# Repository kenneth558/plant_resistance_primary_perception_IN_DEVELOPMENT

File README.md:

[Project now moved to wiki.  Simply click here](https://github.com/kenneth558/plant_resistance_primary_perception/wiki/Entanglement-GWAAMC), and thank you for correcting your link records!

[Project purchase and building instructions here](https://github.com/kenneth558/plant_resistance_primary_perception/tree/Free/Where%20to%20find%20everything%20for%20making%20your%20own%20GWAAMC%20device)

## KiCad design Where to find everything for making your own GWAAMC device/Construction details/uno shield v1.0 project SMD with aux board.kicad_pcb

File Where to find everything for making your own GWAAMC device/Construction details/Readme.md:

The U numbers in these depictions are off by one since the U numbering scheme changed 06 Sep 2019

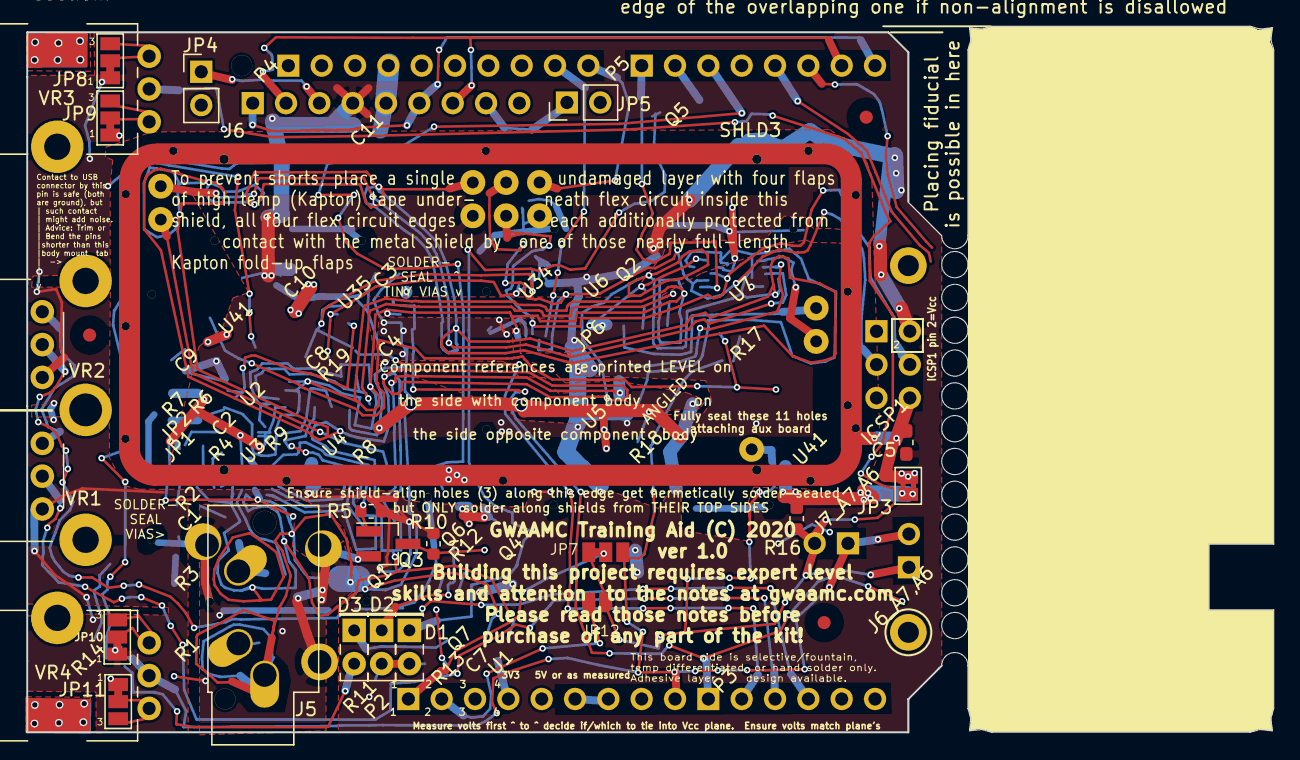
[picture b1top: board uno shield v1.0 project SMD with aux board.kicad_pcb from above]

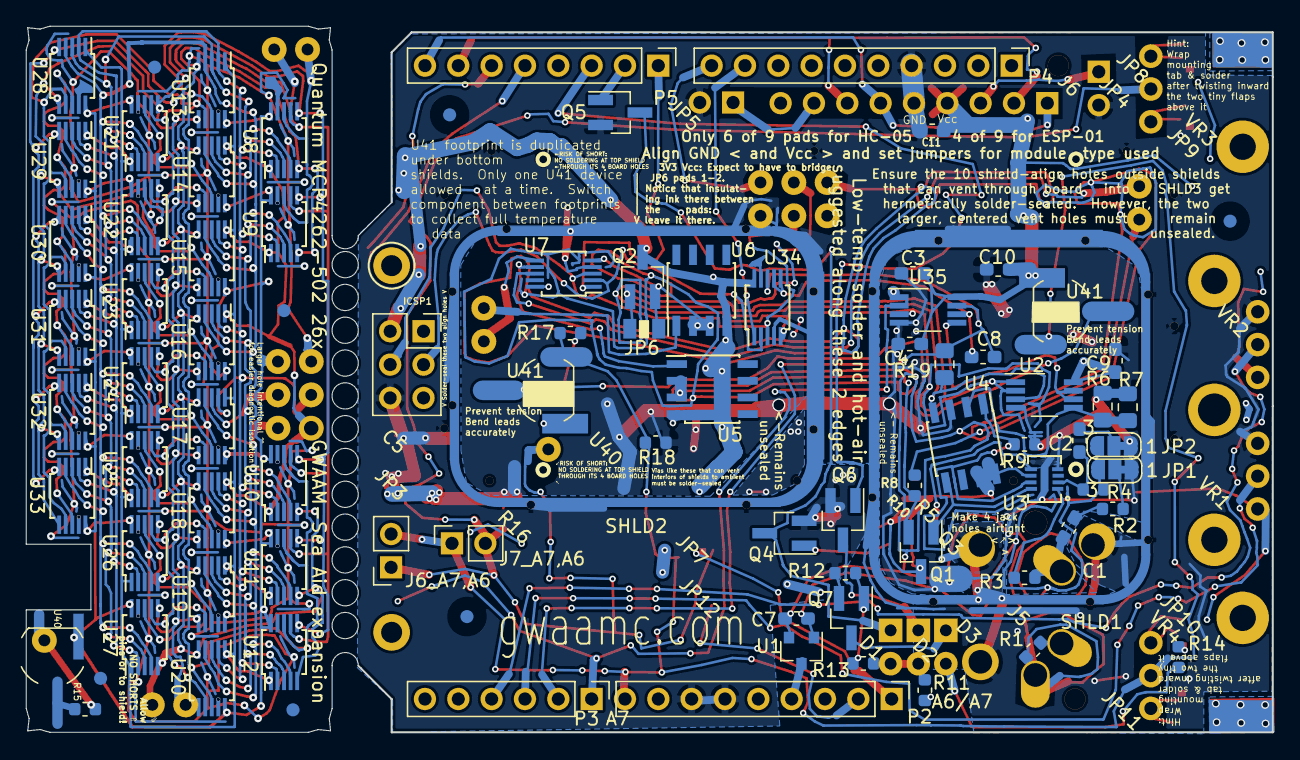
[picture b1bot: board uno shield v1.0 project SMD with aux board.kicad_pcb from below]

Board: 2 copper layers, 95.0 x 53.8 mm, 169 parts (100 on the bottom side), 59 nets.

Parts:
BreakGuide: MountingHole_2.1mm; BreakguideHole
BreakGuide#2, BreakGuide#3, BreakGuide#4, BreakGuide#5, BreakGuide#6, BreakGuide#7, BreakGuide#8, BreakGuide#9, BreakGuide#10, BreakGuide#11, BreakGuide#12, BreakGuide#13, BreakGuide#14, BreakGuide#15, BreakGuide#16, BreakGuide#17, BreakGuide#18, BreakGuide#19, BreakGuide#20, BreakGuide#21, BreakGuide#22, BreakGuide#23, BreakGuide#24, BreakGuide#25, BreakGuide#26, BreakGuide#27, BreakGuide#28: MountingHole_2.1mm; BreakguideHole
C1: 390 pF; C_0603_1608Metric_Pad1.05x0.95mm_HandSolder
C2: .22 µF; C_0603_1608Metric_Pad1.05x0.95mm_HandSolder
C3, C5: 10 µF; C_0603_1608Metric_Pad1.05x0.95mm_HandSolder
C4, C11: 0.1 µF; C_0603_1608Metric_Pad1.05x0.95mm_HandSolder
C7: 1uF; C_0603_1608Metric_Pad1.05x0.95mm_HandSolder
C8: 10-51 pF; C_0603_1608Metric_Pad1.05x0.95mm_HandSolder
C9, C10: .022 µF; C_0603_1608Metric_Pad1.05x0.95mm_HandSolder
D1: Red: Electrodes shorted; LED_Rectangular_W5.0mm_H2.0mm
D2: Yellow: Inadequate electrode conductance; LED_Rectangular_W5.0mm_H2.0mm_yellow
D3: Green: Proper electrode conductance; LED_Rectangular_W5.0mm_H2.0mm_green
FID1, FID2, FID3, FID4, FID5, FID6: Fiducial_1mm_Mask3mm
FID 7, FID 7#2, FID 7#3, FID 88: Fiducial_1mm_Mask3mm
ICSP1: ICSP Socket; PinSocket_2x03_P2.54mm_Vertical
J1, J2, J3, J4: CONN_01X01; TestPoint_Keystone_5010-5014_Multipurpose
J5: Conn_3.5mm; Jack_3.5mm_CUI_SJ1-3534NS_Horizontal_CircularHoles
J6: Conn_01x09_Female; PinSocket_1x09_P2.54mm_Vertical
J6_A7,A6: Conn_01x02_Male; PinSocket_1x02_P2.54mm_Vertical
J7, J8, J9, J10, J11, J12, J13, J14, J15, J16, J17: Conn_01x01_Male; Hole_0.5mm
J7_A7,A6: Conn_01x02_Female; PinSocket_1x02_P2.54mm_Vertical
J17#2, J18, J19, J20, J23, J24, J24#2, J24#3, J24#4, J25, J32: Conn_01x01_Male; Banana_Jack_2mm_1Pin
JP1: C1_leak_mitigator; SolderJumper-3_P1.3mm_Bridged12_RoundedPad1.0x1.5mm_NumberL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
JP2: C2_bias_reducer; SolderJumper-3_P1.3mm_Bridged12_RoundedPad1.0x1.5mm_NumberL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
JP3: Cut_JP3_if_installing_HX711_option; SolderJumper-2_P1.3mm_Bridged2Bar_Pad1.0x1.5mm
JP4: HC-05_EN/KEY; PinHeader_1x02_P2.54mm_Vertical
JP5: HC-05_KEY/STATE_LED; PinHeader_1x02_P2.54mm_Vertical
JP6: Bridge in 3Vdc; SolderJumper-2_P1.3mm_Open_Pad1.0x1.5mm
JP7: SolderJumper_3_Bridged12; SolderJumper-3_P1.3mm_Bridged12_Pad1.0x1.5mm
JP8, JP9, JP10, JP11: SolderJumper_3_Bridged12; SolderJumper-3_P1.3mm_Bridged12_Pad1.0x1.5mm_NumberLabels
JP12: SolderJumper_2_Open; SolderJumper-2_P1.3mm_Open_RoundedPad1.0x1.5mm
P2: Power; PinHeader_1x09_P2.54mm_Vertical
P3: Analog; PinHeader_1x06_P2.54mm_Vertical
P4: Digital; PinHeader_1x10_P2.54mm_Vertical
P5: Digital; PinHeader_1x08_P2.54mm_Vertical
Q1, Q2: MMBF5460 (2N5460); SOT-23_Handsoldering
Q3, Q4, Q5, Q6, Q7: DMN601K-7; SOT-23_Handsoldering
R1, R2: 100 Ω; R_0603_1608Metric
R3: 3.9 KΩ; R_0603_1608Metric
R4: 21 KΩ; R_0603_1608Metric
R5, R9: 10 KΩ; R_0603_1608Metric
R6: 44.2 KΩ 0.1% 0.1W(1/10W) ±10ppm/°C (1676343-2); R_0805_2012Metric_Pad1.15x1.40mm_HandSolder
R7: 22.6 KΩ 0.1% 0.125W(1/8W) ±10ppm/°C (ERA6ARB2262V); R_0805_2012Metric_Pad1.15x1.40mm_HandSolder
R8: 15 KΩ; R_0603_1608Metric
R10, R12, R13: 1 MΩ; R_0603_1608Metric
R11, R14: 470 Ω; R_0603_1608Metric
R15, R17: 14.7 KΩ 0.1% 0.063W ±25ppm/°C (NTR06B1472CTRF); R_0603_1608Metric
R16, R18: 390 KΩ 0.1% 0.063W ±25ppm/°C (CPF0603B390KE1); R_0603_1608Metric
R19: Optional_Rf; R_0805_2012Metric_Pad1.15x1.40mm_HandSolder
SHLD1, SHLD2: MS263-20C (cover only of MS263-20); Masach_Tech_MS26320_26x19.50mm
SHLD3: MS544-10C (cover only of MS544-10); Masach_Tech_MS54410_54x23.90mm
U1: 3V LDO; SOT-23
U2, U35: OPA2388IDGKR; VSSOP-8_3.0x3.0mm_P0.65mm
U3: ADL5315; ADL5315ACPZ-R7
U4: REF200AU; SOIC-8_3.9x4.9mm_P1.27mm
U5, U6: LM334M; SOIC-8_3.9x4.9mm_P1.27mm
U7: MCP4262-503E/UN; MSOP-10_3x3mm_P0.5mm
U8, U9, U10, U11, U12, U13, U14, U15, U16, U17, U18, U19, U20, U21, U22, U23, U24, U25, U26, U27, U28, U29, U30, U31, U32, U33, U34: MCP4262-502E/UN; MSOP-10_3x3mm_P0.5mm
U40: LM334Z; TO-92_Spread_for_LM334Z
U41, U41#2: LM334Z; TO-92_full pads_for_LM334Z
VR1, VR2: 50 KΩ; Potentiometer_Bourns_PTV09A-2_Single_Horizontal
VR3, VR4: 20 KΩ; Potentiometer_Bourns_PTV09A-1_Single_Vertical

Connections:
+3V3: P2.4, U1.3
/1st_stage_guard_ring: C7.1, J12.1, J24#3.1, JP1.3, JP2.3, R4.2, U1.2
/2nd_stage_ring: R9.1, U3.7, U4.1
/3rd_stage_guard_ring: U2.1, U2.2, U34.5, U35.3
/5(**): P5.3, Q6.1
/6(**): P5.2, Q5.1
/7: P5.1, U7.1
/8: J14.1, J23.1, P4.10, U8.1, U9.1, U10.1, U11.1, U12.1, U13.1, U14.1, U15.1, U16.1, U17.1, U18.1, U19.1, U20.1, U21.1, U22.1, U23.1, U24.1, U25.1, U26.1, U27.1, U28.1, U29.1, U30.1, U31.1, U32.1, U33.1
/9(**): P4.9, U34.1
/A0: P3.1, U35.1, U35.2
/A1: C8.1, P3.2, R19.1, U34.8, U35.7
/A2: P3.3, VR1.2
/A3: P3.4, VR2.2
/A6: J6_A7,A6.1, J7_A7,A6.2, J17.1, J17#2.1, JP7.1, JP12.2, R15.2, R16.1, U40.3, VR3.2
/A6-A7: JP7.2, P2.1
/A7: J6_A7,A6.2, J7_A7,A6.1, JP7.3, P2.9, R17.2, R18.1, U41.3, U41#2.3, VR4.2
/CFG-IOREF-A6: JP12.1, P2.2
/J5-PadR: C1.1, J5.R, R3.1
/J5-PadT: J5.T, R1.2
/MOSI(1): ICSP1.4, J16.1, J24#2.1, U7.3, U8.3, U9.3, U10.3, U11.3, U12.3, U13.3, U14.3, U15.3, U16.3, U17.3, U18.3, U19.3, U20.3, U21.3, U22.3, U23.3, U24.3, U25.3, U26.3, U27.3, U28.3, U29.3, U30.3, U31.3, U32.3, U33.3, U34.3
/Rx: J6.1, J6.6, P5.8
/SCK(1): ICSP1.3, J15.1, J25.1, U7.2, U8.2, U9.2, U10.2, U11.2, U12.2, U13.2, U14.2, U15.2, U16.2, U17.2, U18.2, U19.2, U20.2, U21.2, U22.2, U23.2, U24.2, U25.2, U26.2, U27.2, U28.2, U29.2, U30.2, U31.2, U32.2, U33.2, U34.2
/Tx: J6.2, J6.7, P5.7
/U8-Pad5: J8.1, J19.1, U7.6, U8.5, U9.5, U10.5, U11.5, U12.5, U13.5, U14.5, U15.5, U16.5, U17.5, U18.5, U19.5, U20.5, U21.5, U22.5, U23.5, U24.5, U25.5, U26.5, U27.5, U28.5, U29.5, U30.5, U31.5, U32.5, U33.5
/U8-Pad6: J7.1, J20.1, U6.1, U8.6, U9.6, U10.6, U11.6, U12.6, U13.6, U14.6, U15.6, U16.6, U17.6, U18.6, U19.6, U20.6, U21.6, U22.6, U23.6, U24.6, U25.6, U26.6, U27.6, U28.6, U29.6, U30.6, U31.6, U32.6, U33.6
/U8-Pad7: J10.1, J32.1, R8.1, U8.7, U9.7, U10.7, U11.7, U12.7, U13.7, U14.7, U15.7, U16.7, U17.7, U18.7, U19.7, U20.7, U21.7, U22.7, U23.7, U24.7, U25.7, U26.7, U27.7, U28.7, U29.7, U30.7, U31.7, U32.7, U33.7
/U8-Pad8: J11.1, J18.1, U7.8, U8.8, U9.8, U10.8, U11.8, U12.8, U13.8, U14.8, U15.8, U16.8, U17.8, U18.8, U19.8, U20.8, U21.8, U22.8, U23.8, U24.8, U25.8, U26.8, U27.8, U28.8, U29.8, U30.8, U31.8, U32.8, U33.8
GNDA: C3.2, C4.2, C7.2, C9.1, C10.1, J5.S, JP1.1, JP2.1, JP3.1, R1.1, R6.2, R7.2, R9.2, R16.2, R18.2, U1.1, U2.4, U3.4, U3.9, U4.3, U35.4
GNDD: C5.2, C11.1, ICSP1.6, J5.G, J6.5, J13.1, J24.1, JP3.2, JP4.2, JP5.2, JP9.1, JP11.1, P2.6, P2.7, P4.4, Q3.2, Q4.2, Q5.2, Q6.2, Q7.2, R12.1, SHLD1.1, SHLD2.1, SHLD3.1, U7.4, U8.4, U9.4, U10.4, U11.4, U12.4, U13.4, U14.4, U15.4, U16.4, U17.4, U18.4, U19.4, U20.4, U21.4, U22.4, U23.4, U24.4, U25.4, U26.4, U27.4, U28.4, U29.4, U30.4, U31.4, U32.4, U33.4, U34.4, VR1.1, VR2.1
unnamed: C1.2, R2.1
unnamed: C2.1, R4.1, U3.2
unnamed: C2.2, JP2.2
unnamed: C8.2, U34.6, U34.7, U35.6
unnamed: D1.1, Q4.3, Q5.3
unnamed: D1.2, D2.2, R11.2, R13.2
unnamed: D2.1, Q6.3
unnamed: D3.1, Q7.3
unnamed: D3.2, R14.2
unnamed: J6.3, JP4.1
unnamed: J6.8, JP5.1
unnamed: JP1.2, R2.2
unnamed: JP6.1, Q2.2, U6.2, U6.3, U7.5
unnamed: JP6.2, Q2.1, R19.2, U2.3, U4.4
unnamed: JP8.2, JP8.3, VR3.3
unnamed: JP9.2, JP9.3, VR3.1
unnamed: JP10.2, JP10.3, VR4.3
unnamed: JP11.2, JP11.3, VR4.1
unnamed: Q1.1, U3.8, U4.5
unnamed: Q1.2, R8.2, U5.2, U5.3
unnamed: Q3.1, R5.1, U3.5
unnamed: Q3.3, Q4.1, R10.2
unnamed: Q7.1, R12.2, R13.1
unnamed: R3.2, U3.1
unnamed: R6.1, R7.1, U2.5, U4.2
unnamed: R15.1, U40.2
unnamed: R17.1, U41.2, U41#2.2
unnamed: U2.6, U2.7, U35.5
unnamed: U5.1, U7.7
VCC: C3.1, C4.1, C5.1, C9.2, C10.2, C11.2, ICSP1.2, J6.4, J9.1, J24#4.1, JP8.1, JP10.1, Q1.3, Q2.3, R5.2, R10.1, R11.1, R14.1, U2.8, U3.6, U4.7, U4.8, U5.4, U6.4, U7.10, U8.10, U9.10, U10.10, U11.10, U12.10, U13.10, U14.10, U15.10, U16.10, U17.10, U18.10, U19.10, U20.10, U21.10, U22.10, U23.10, U24.10, U25.10, U26.10, U27.10, U28.10, U29.10, U30.10, U31.10, U32.10, U33.10, U34.10, U35.8, U40.1, U41.1, U41#2.1, VR1.3, VR2.3

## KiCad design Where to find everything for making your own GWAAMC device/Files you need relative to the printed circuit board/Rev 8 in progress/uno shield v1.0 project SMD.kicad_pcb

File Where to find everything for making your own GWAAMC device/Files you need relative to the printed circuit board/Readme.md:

To buy your own PCB you'll send [this file](https://github.com/kenneth558/plant_resistance_primary_perception/blob/Free/Where%20to%20find%20everything%20for%20making%20your%20own%20GWAAMC%20device/Files%20you%20need%20relative%20to%20the%20printed%20circuit%20board/v1.0/gerbers%20uno%20shield%20v1.0%20main%20board%20only.zip) and [this file](https://github.com/kenneth558/plant_resistance_primary_perception/blob/Free/Where%20to%20find%20everything%20for%20making%20your%20own%20GWAAMC%20device/Files%20you%20need%20relative%20to%20the%20printed%20circuit%20board/v1.0/Quantum%20MCP4262-502%2026x%20expansion%20for%20GWAAM-Sea%20Aid%20gerbers.zip) to OSH Park, BasicPCB, PCBWay, or to wherever you choose, then pay and wait.  [This](https://oshpark.com/shared_projects/fb4IIqwY) is the OSH Park project link for even easier ordering of the main board...and [aux board](https://oshpark.com/shared_projects/tLj5WHoL) at OSH Park. A minimum quantity purchase of 3-5 boards is normal.  

*NEW!* [Boards combined](https://github.com/kenneth558/plant_resistance_primary_perception/blob/Free/Where%20to%20find%20everything%20for%20making%20your%20own%20GWAAMC%20device/Files%20you%20need%20relative%20to%20the%20printed%20circuit%20board/v1.0/combined%20main%20plus%20aux%20on%20single%20board/gerbers%20uno%20shield%20v1.0%20PCB%20sections%20combined.zip) but able to be carefully separated before or after after components get soldered down.  May be temporarily air-wired into operation while still in one piece.  This style may help you in PCB soliciting quotes and ordering, but it will be risky separating them due to proximity to board edges of conducting traces.  [Boards combined OSH Park project](https://oshpark.com/shared_projects/ZdywHSTk).

I actually can't recommend the ENIG boards because industry wisdom is now that the gold on ENIG boards is better washed off ("cleansed") by double tinning - I've found that I have to wash it off, anyway, to get acceptable results.  That negates the entire advantage of ENIG's flat pads for fine pitch components because it takes several hours to double tin and flatten out the pads.  Then on top of that, the last HASL boards I ordered had taken sufficient precautions to give me flat pads on the side of the board it mattered most for me...without me even suggesting it!  That left only one single fine-pich component for me to worry about, and I took care of that easily with Kapton tape/hot air/hot iron pad flattening.  Besides, ENIG boards are limited to a six month shelf life.  So I'm going to recommend just getting 2oz,TG170+, lead-free HASL boards, requesting the fab house try to put flattest pads on the surface with the most fine-pitch packages, and flatten any other fine pitch pads yourself.  On the ENIG boards, a little solder flux helps conduct the heat and makes things less frustrating.  If there is any chance you'll use bismuth solder and you're going the HASL route, specify "lead-free" HASL or the solder won't stick to the pads.

If you are determined to purchase ENIG boards, you can't go wrong with OSH Park because their [rigid] boards handle the heat so well without the copper delaminating nor heat damage occuring otherwise.  I've read they use TG170.  Chinese boards default to TG140 and will darken and char at much lower heat levels than OSH Park boards, and their copper delaminates from the board at lower heat levels than OSH Park's 2 oz. boards.  OSH Park's flex boards, however, won't handle full-scale air heating without risking bubbles, but if you're careful to pop those bubbles while they're small, you should be fine.

When I got sloppy with the ENIG boards by putting on way more solder than I needed to, I did pull pads up, so you might as well be neat and frugal while tinning, including only tinning one side - the side you need to tin - on the plated through holes.  Here's how I convert ENIG to lead-free HASL:  
- I use hot air, 
- press lead-free solid wire solder against all gold that needs to be soldered to until the gold is absorbed into molten solder
- I do this twice
- I scoop the surface flat with hot air, then convert to bismuth (low temperature) solder with one more pass and scoop flat again.  If you've been thorough on every step, your board is ready to accept bismuth cream and placed components and heat to melt the low-temperature solder.

Stencil stock thickness should be no more than 4 mil (0.1mm).  Don't trust stacking stencils to obtain that thickness because the stencil apertures must have smooth enough walls not to pull the paste solder off the board when removed.  Remove the stencil quick enough after applying the paste that the paste doesn't dry enough to adhere to the stencil apertures walls.

Stencils are [here](https://github.com/kenneth558/plant_resistance_primary_perception/blob/Free/Where%20to%20find%20everything%20for%20making%20your%20own%20GWAAMC%20device/Files%20you%20need%20relative%20to%20the%20printed%20circuit%20board/v1.0/F%26B%20Paste%20stencils%20uno%20shield%20v1.0%20main%20board%20only.zip).

*NEW!* Combined board stencils [here](https://github.com/kenneth558/plant_resistance_primary_perception/blob/Free/Where%20to%20find%20everything%20for%20making%20your%20own%20GWAAMC%20device/Files%20you%20need%20relative%20to%20the%20printed%20circuit%20board/v1.0/combined%20main%20plus%20aux%20on%20single%20board/F%26B%20Paste%20stencils%20uno%20shield%20v1.0%20PCB%20sections%20combined.zip).

Bare board renderings courtesy of OSH Park

[Go to populating the board or the populated board instead](https://github.com/kenneth558/plant_resistance_primary_perception/tree/Free/Where%20to%20find%20everything%20for%20making%20your%20own%20GWAAMC%20device)

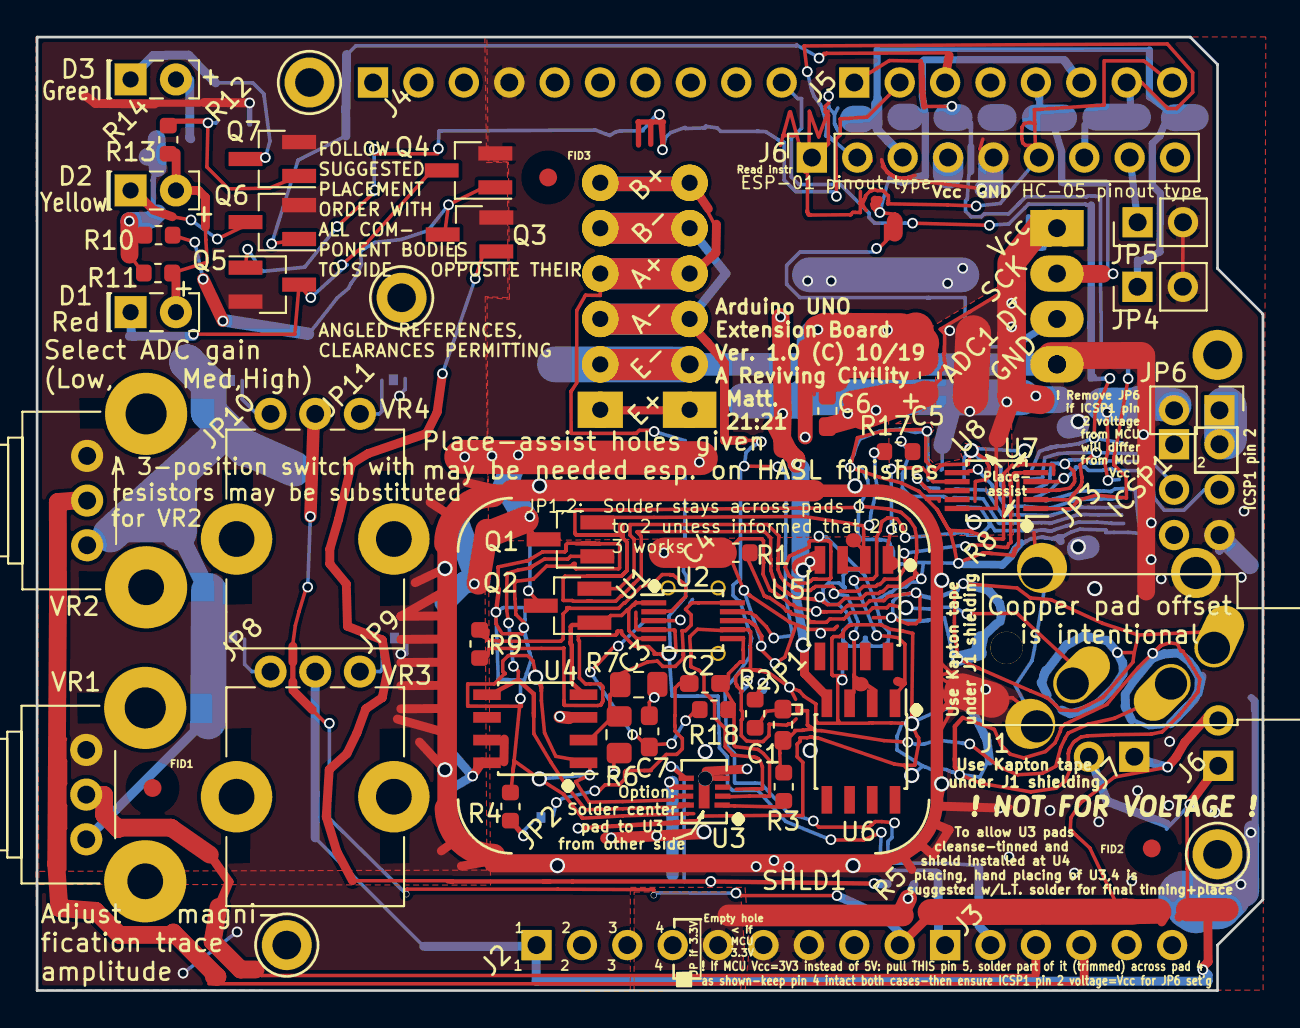
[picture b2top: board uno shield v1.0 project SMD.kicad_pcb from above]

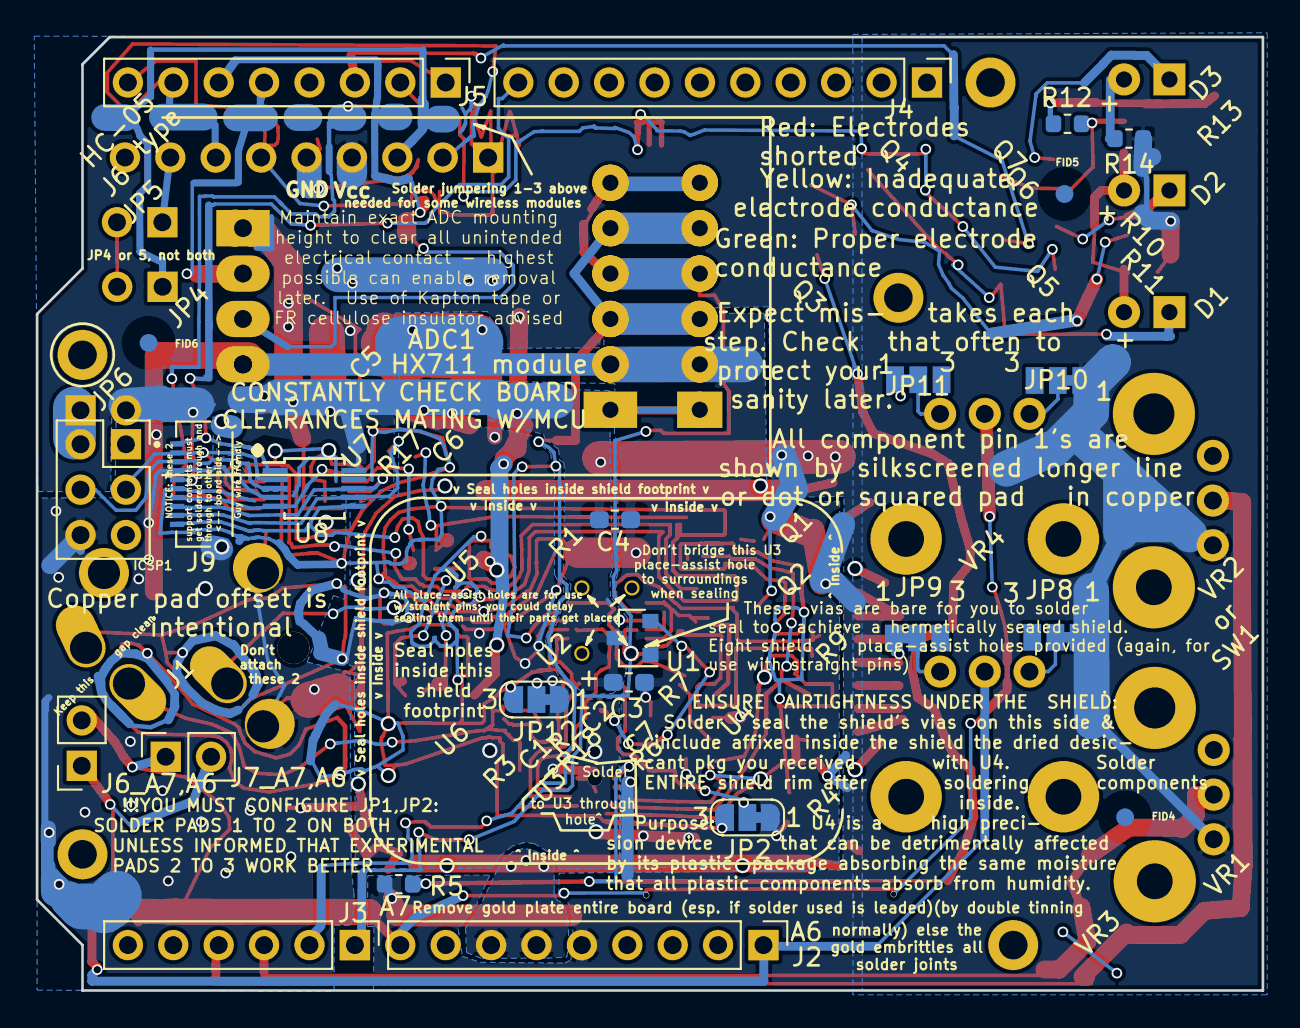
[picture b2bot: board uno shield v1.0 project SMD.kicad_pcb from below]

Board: 2 copper layers, 68.6 x 53.3 mm, 82 parts (27 on the bottom side), 57 nets.

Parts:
ADC1: HX711 module
C1: 390 pF; C_0603_1608Metric_Pad1.05x0.95mm_HandSolder
C2: .22 µF; C_0603_1608Metric_Pad1.05x0.95mm_HandSolder
C3, C5: 2.2 µF; C_0603_1608Metric_Pad1.05x0.95mm_HandSolder
C4, C6: 0.1 µF; C_0603_1608Metric_Pad1.05x0.95mm_HandSolder
C7: 1uF; C_0603_1608Metric_Pad1.05x0.95mm_HandSolder
D1: Red: Electrodes shorted; LED_Rectangular_W5.0mm_H2.0mm
D2: Yellow: Inadequate electrode conductance; LED_Rectangular_W5.0mm_H2.0mm_yellow
D3: Green: Proper electrode conductance; LED_Rectangular_W5.0mm_H2.0mm_green
FID1, FID2, FID3: Front Fiducial; Fiducial_1mm_Mask3mm
FID4, FID5, FID6: Back Fiducial; Fiducial_1mm_Mask3mm
ICSP1: ICSP Socket; PinSocket_2x03_P2.54mm_Vertical
J1: Conn_3.5mm; Jack_3.5mm_CUI_SJ1-3534NS_Horizontal_CircularHoles
J2: Power; PinHeader_1x09_P2.54mm_Vertical
J3: Analog; PinHeader_1x06_P2.54mm_Vertical
J4: Digital; PinHeader_1x10_P2.54mm_Vertical
J5: Digital; PinHeader_1x08_P2.54mm_Vertical
J6: Conn_01x09_Female; PinSocket_1x09_P2.54mm_Vertical
J6_A7,A6: Conn_01x02_gender_unknown; PinSocket_1x02_P2.54mm_Vertical
J7_A7,A6: Conn_01x02_Female; PinSocket_1x02_P2.54mm_Vertical
J9: TE_1-2328702-0
JP1: C1_leak_mitigator; SolderJumper-3_P1.3mm_Bridged12_RoundedPad1.0x1.5mm_NumberL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
JP2: C2_bias_reducer; SolderJumper-3_P1.3mm_Bridged12_RoundedPad1.0x1.5mm_NumberL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
JP4: HC-05_EN/KEY; PinHeader_1x02_P2.54mm_Vertical
JP5: HC-05_KEY/STATE_LED; PinHeader_1x02_P2.54mm_Vertical
JP6: Remove JP6 if MCU is 3V3 but MCU board sends 5V u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; PinHeader_1x02_P2.54mm_Vertical
JP8, JP9, JP10, JP11: SolderJumper_3_Bridged12; SolderJumper-3_P1.3mm_Bridged12_Pad1.0x1.5mm_NumberLabels
NT1: Net-Tie_2; NetTie-2_THT_Pad1.0mm
NT2, NT3, NT4, NT5, NT6, NT7: Net-Tie_2; NetTie-2_HX711_THT_Pad1.0mm
P1, P2, P3, P4: CONN_01X01; TestPoint_Keystone_5010-5014_Multipurpose
Q1, Q2: MMBF5460 (2N5460); SOT-23_Handsoldering
Q3, Q4, Q5, Q6, Q7: DMN601K-7; SOT-23_Handsoldering
R1, R2: 100 Ω; R_0603_1608Metric
R3: 3.9 KΩ; R_0603_1608Metric
R4, R5: 10 KΩ; R_0603_1608Metric
R6: 44.2 KΩ 0.1% 0.1W(1/10W) ±10ppm/°C (1676343-2); R_0805_2012Metric_Pad1.15x1.40mm_HandSolder
R7: 22.6 KΩ 0.1% 0.125W(1/8W) ±10ppm/°C (ERA6ARB2262V); R_0805_2012Metric_Pad1.15x1.40mm_HandSolder
R9: 27 Ω; R_0603_1608Metric
R10, R12, R13: 1 MΩ; R_0603_1608Metric
R11, R14: 470 Ω; R_0603_1608Metric
R17: 15 KΩ; R_0603_1608Metric
R18: 21 KΩ; R_0603_1608Metric
SHLD1: Device_RF_Shield_Two_Pieces_but_use_only_TOP; Masach_Tech_MS26320_26x19.50mm
U1: 3V LDO; SOT-23
U2: AD8244ARMZ; MSOP-10_3x3mm_P0.5mm
U3: ADL5315ACPZ-R7
U4: REF200AU; SOIC-8_3.9x4.9mm_P1.27mm
U5, U6: LM334M; SOIC-8_3.9x4.9mm_P1.27mm
U7: MCP4262-503E/UN; MSOP-10_3x3mm_P0.5mm
U8: - U33 all in parallel MCP4262-502E/UN; MSOP-10_3x3mm_P0.5mm
VR1, VR2: 200 KΩ; Potentiometer_Bourns_PTV09A-2_Single_Horizontal
VR3, VR4: 200 KΩ; Potentiometer_Bourns_PTV09A-1_Single_Vertical

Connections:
+5V: ADC1.VCC, C3.1, C4.1, C5.1, C6.2, J2.5, J6.4, J9.5, JP6.2, JP8.1, JP10.1, Q1.3, Q2.3, R5.2, R10.1, R11.1, R14.1, U1.3, U2.3, U3.6, U4.7, U4.8, U5.4, U6.4, U7.10, U8.10, VR1.3, VR2.3
/1st_stage_guard_trace: J9.6, JP1.3, JP2.3, U2.7
/2: ADC1.DT, J5.6
/2nd_stage_guard_trace: R4.1, U3.7, U4.1
/3(**): ADC1.SCK, J5.5
/3rd_stage_guard_trace: R9.1, U2.2
/5(**): J5.3, Q6.1
/6(**): J5.2, Q5.1
/7: J5.1, U7.1
/8: J4.10, J9.1, U8.1
/A0: ADC1.Aplus, ADC1.Aplus_dup, ADC1.Bplus, ADC1.Bplus_dup, J3.1, NT2.1, NT2.2, NT3.1, NT3.2, R9.2, U2.4
/A1: ADC1.Aminus, ADC1.Aminus_dup, ADC1.Bminus, ADC1.Bminus_dup, J3.2, NT4.1, NT4.2, NT5.1, NT5.2, U2.9
/A2: J3.3, VR1.2
/A3: J3.4, VR2.2
/A6: J2.1, J6_A7,A6.1, J7_A7,A6.2, VR3.2
/A7: J2.9, J6_A7,A6.2, J7_A7,A6.1, VR4.2
/MOSI(1): ICSP1.4, J9.3, U7.3, U8.3
/Rx: J5.8, J6.1, J6.6
/SCK(1): ICSP1.3, J9.2, U7.2, U8.2
/Tx: J5.7, J6.2, J6.7
/U8-Pad5: J9.7, U7.6, U8.5
/U8-Pad6: J9.10, U6.1, U8.6
/U8-Pad7: J9.9, R17.1, U8.7
/U8-Pad8: J9.8, U7.8, U8.8
GNDA: ADC1.GNDA, ADC1.GNDA_dup, C3.2, C4.2, C5.2, C6.1, C7.2, J1.S, JP1.1, JP2.1, NT1.1, NT7.1, NT7.2, R1.1, R4.2, R6.2, R7.2, U1.1, U2.8, U3.4, U3.9, U4.3
GNDD: ADC1.GND, ICSP1.6, J1.G, J2.6, J2.7, J4.4, J6.5, J9.4, J9.S1, J9.S2, JP4.2, JP5.2, JP9.1, JP11.1, NT1.2, Q3.2, Q4.2, Q5.2, Q6.2, Q7.2, R12.1, SHLD1.1, U7.4, U8.4, VR1.1, VR2.1
unnamed: ADC1.Eplus, NT6.1
unnamed: ADC1.Eplus_dup, NT6.2
unnamed: C1.1, J1.T, R3.1
unnamed: C1.2, R2.1
unnamed: C2.1, R18.1, U2.6, U3.2
unnamed: C2.2, JP2.2
unnamed: C7.1, R18.2, U1.2
unnamed: D1.1, Q4.3, Q5.3
unnamed: D1.2, D2.2, R11.2, R13.2
unnamed: D2.1, Q6.3
unnamed: D3.1, Q7.3
unnamed: D3.2, R14.2
unnamed: ICSP1.2, JP6.1
unnamed: J1.R, R1.2
unnamed: J6.3, JP4.1
unnamed: J6.8, JP5.1
unnamed: JP1.2, R2.2
unnamed: JP8.2, VR3.3
unnamed: JP9.2, VR3.1
unnamed: JP10.2, VR4.3
unnamed: JP11.2, VR4.1
unnamed: Q1.1, U3.8, U4.5
unnamed: Q1.2, R17.2, U5.2, U5.3
unnamed: Q2.1, U2.1, U2.5, U4.4
unnamed: Q2.2, U6.2, U6.3, U7.5
unnamed: Q3.1, R5.1, U3.5
unnamed: Q3.3, Q4.1, R10.2
unnamed: Q7.1, R12.2, R13.1
unnamed: R3.2, U3.1
unnamed: R6.1, R7.1, U2.10, U4.2
unnamed: U5.1, U7.7

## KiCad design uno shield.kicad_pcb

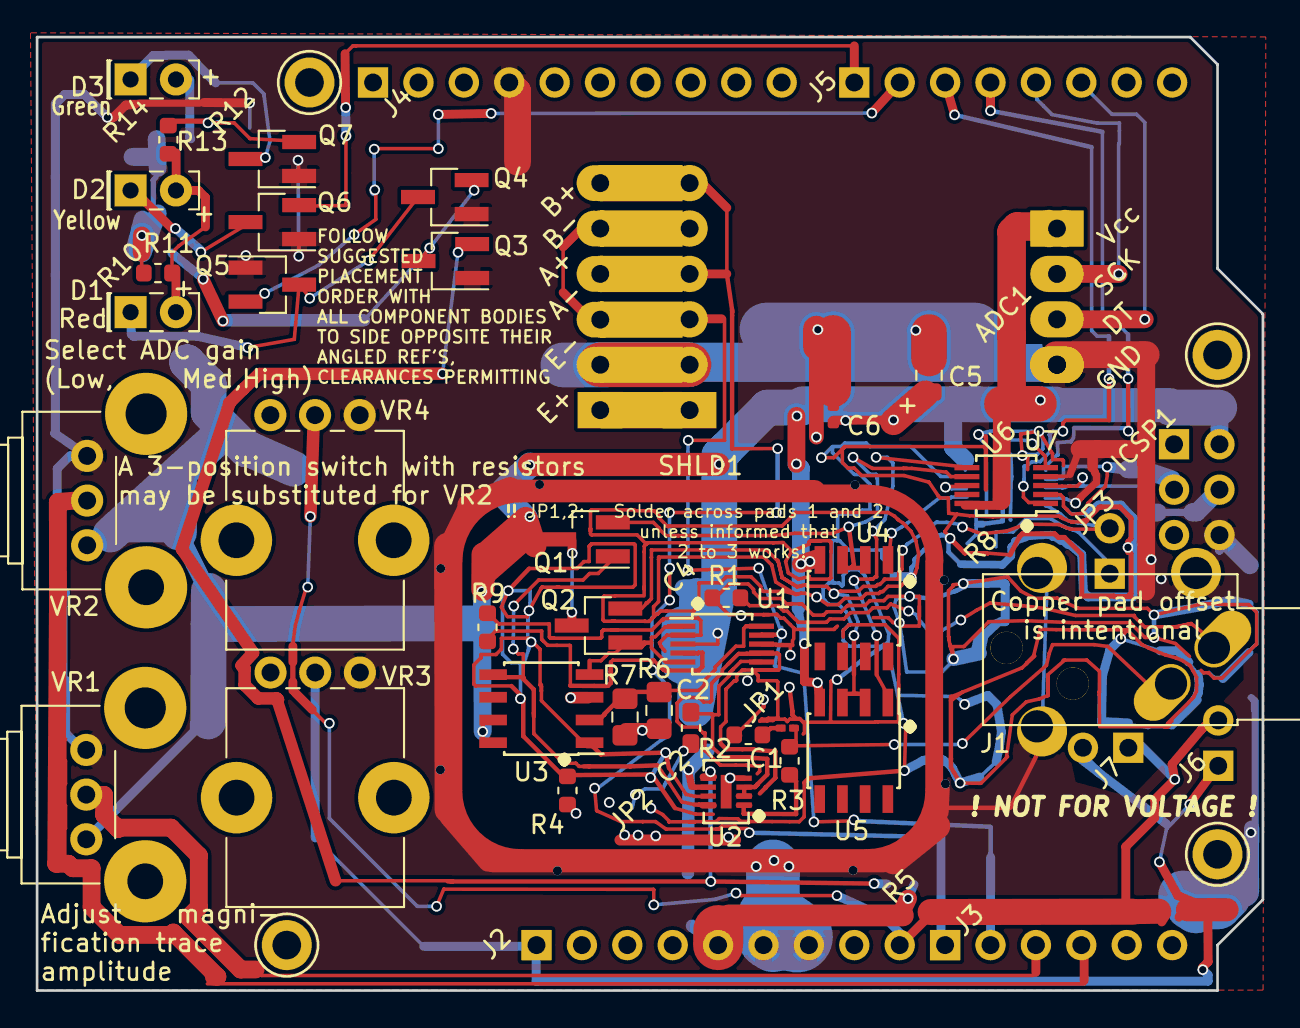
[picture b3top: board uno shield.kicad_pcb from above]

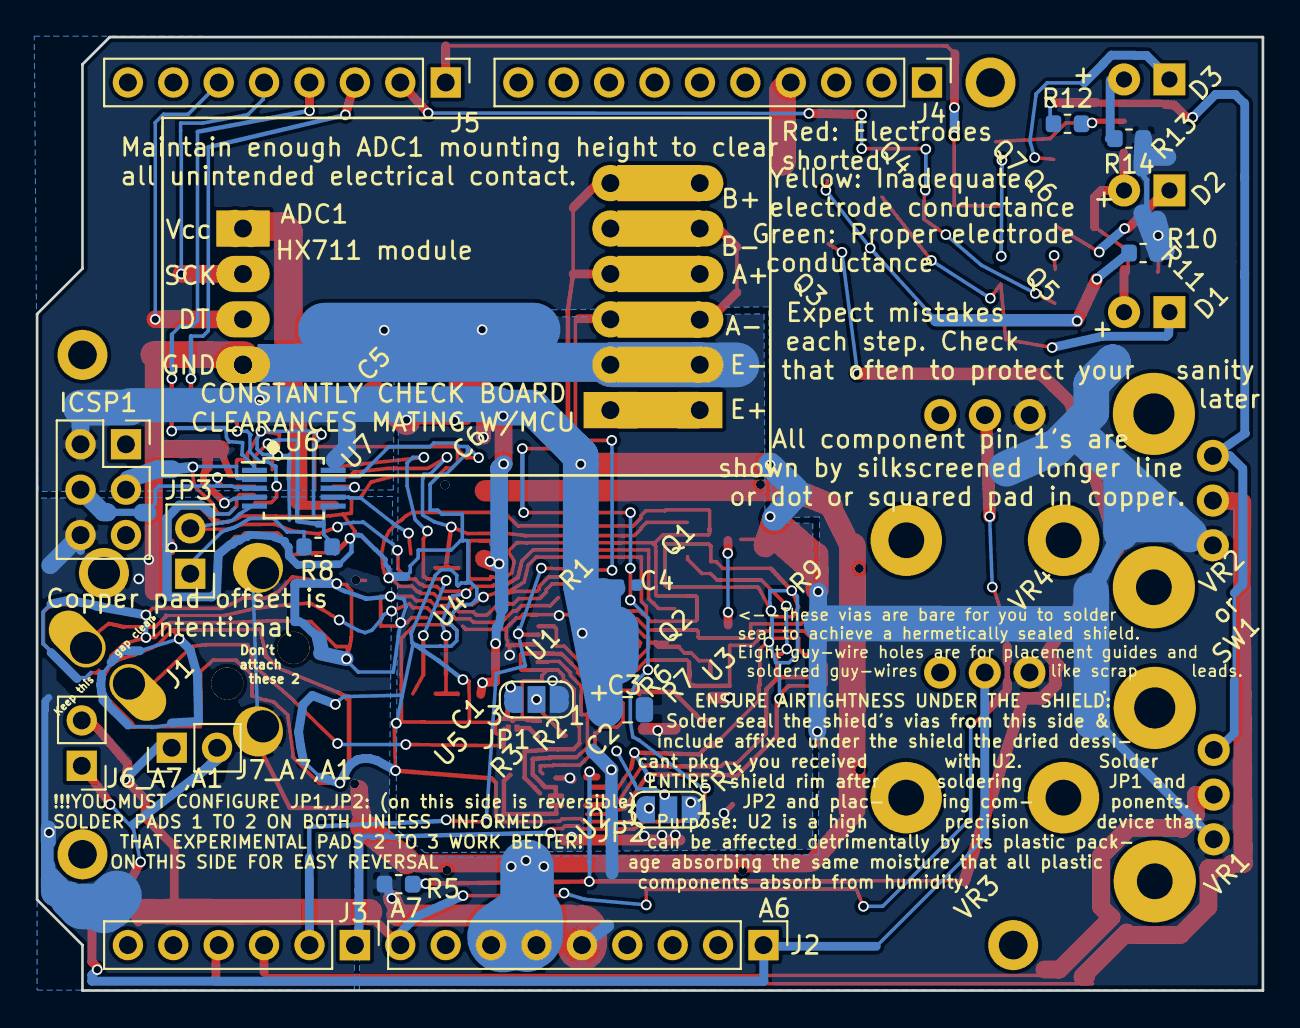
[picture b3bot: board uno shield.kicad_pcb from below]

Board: 2 copper layers, 68.6 x 53.3 mm, 59 parts (20 on the bottom side), 45 nets.

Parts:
ADC1: HX711 module
C1: 390 pF; C_0201_0603Metric
C2: .22 µF; C_0603_1608Metric_Pad1.05x0.95mm_HandSolder
C3, C5: 2.2 µF; C_0805_2012Metric
C4, C6: 0.1 µF; C_0402_1005Metric
D1: Red: Electrodes shorted; LED_Rectangular_W5.0mm_H2.0mm
D2: Yellow: Inadequate electrode conductance; LED_Rectangular_W5.0mm_H2.0mm_yellow
D3: Green: Proper electrode conductance; LED_Rectangular_W5.0mm_H2.0mm_green
ICSP1: ICSP Socket; PinSocket_2x03_P2.54mm_Vertical
J1: Conn_3.5mm; Jack_3.5mm_CUI_SJ1-3534NS_Horizontal_CircularHoles
J2: Power; PinHeader_1x09_P2.54mm_Vertical
J3: Analog; PinHeader_1x06_P2.54mm_Vertical
J4: Digital; PinHeader_1x10_P2.54mm_Vertical
J5: Digital; PinHeader_1x08_P2.54mm_Vertical
J6_A7,A1: Conn_01x02_gender_unknown; PinHeader_1x02_P2.54mm_Vertical
J7_A7,A1: Conn_01x02_Female; PinHeader_1x02_P2.54mm_Vertical
JP1: C1_leak_mitigator; SolderJumper-3_P1.3mm_Open_RoundedPad1.0x1.5mm_NumberLabels
JP2: C2_bias_reducer; SolderJumper-3_P1.3mm_Open_RoundedPad1.0x1.5mm_NumberLabels
JP3: Effect reducer; PinHeader_1x02_P2.54mm_Vertical
NT1: Net-Tie_2; NetTie-2_THT_Pad1.0mm
P1, P2, P3, P4: CONN_01X01; TestPoint_Keystone_5010-5014_Multipurpose
Q1, Q2: MMBF5462 (2N5462); SOT-23_Handsoldering
Q3, Q4, Q5, Q6, Q7: DMN601K-7; SOT-23_Handsoldering
R1, R3, R8: 100 Ω; R_0603_1608Metric
R2: 3.9 KΩ; R_0603_1608Metric
R4, R5: 10 KΩ; R_0603_1608Metric
R6: 44.2 KΩ 0.1% 0.1W(1/10W) ±10ppm/°C (1676343-2); R_0805_2012Metric_Pad1.15x1.40mm_HandSolder
R7: 22.6 KΩ 0.1% 0.125W(1/8W) ±10ppm/°C (ERA6ARB2262V); R_0805_2012Metric_Pad1.15x1.40mm_HandSolder
R9: 27 Ω; R_0603_1608Metric
R10, R12, R13: 1 MΩ; R_0603_1608Metric
R11, R14: 470 Ω; R_0603_1608Metric
SHLD1: Device_RF_Shield_Two_Pieces; Masach_Tech_MS26320_26x19.50mm
U1: AD8244ARMZ; MSOP-10_3x3mm_P0.5mm
U2: ADL5315; ADL5315ACPZ-R7
U3: REF200AU; SOIC-8_3.9x4.9mm_P1.27mm
U4, U5: LM334M; SOIC-8_3.9x4.9mm_P1.27mm
U6: MCP4262-502E_UN; MSOP-10_3x3mm_P0.5mm
U7: MCP4262-104E_UN; MSOP-10_3x3mm_P0.5mm
VR1, VR2: 200 KΩ; Potentiometer_Bourns_PTV09A-2_Single_Horizontal
VR3, VR4: 200 KΩ; Potentiometer_Bourns_PTV09A-1_Single_Vertical

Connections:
+5V: ADC1.VCC, C3.1, C4.1, C5.1, C6.2, ICSP1.2, J2.5, Q1.3, Q2.3, R5.2, R10.1, R11.1, R14.1, U1.3, U2.6, U3.7, U3.8, U4.4, U5.4, U6.10, U7.10, VR1.3, VR2.3, VR3.3, VR4.3
/1st_stage_guard_trace: JP1.3, JP2.3, U1.7
/2: ADC1.DT, J5.6
/2nd_stage_guard_trace: R4.1, U2.7, U3.1
/3(**): ADC1.SCK, J5.5
/3rd_stage_guard_trace: R9.1, U1.2
/4: J5.4, U6.1
/5(**): J5.3, U7.1
/6(**): J5.2, Q5.2
/7: J5.1, Q6.2
/A0: ADC1.Aplus, ADC1.Bplus, J3.1, R9.2, U1.4
/A1: ADC1.Aminus, ADC1.Bminus, J3.2, U1.9
/A2: J3.3, VR1.2
/A3: J3.4, VR2.2
/A6: J2.1, J6_A7,A1.1, J7_A7,A1.2, VR3.2
/A7: J2.9, J6_A7,A1.2, J7_A7,A1.1, VR4.2
/MOSI(1): ICSP1.4, U6.3, U7.3
/SCK(1): ICSP1.3, U6.2, U7.2
GNDA: ADC1.GNDA, C3.2, C4.2, C5.2, C6.1, JP1.1, JP2.1, R1.1, R4.2, R6.2, R7.2, U1.8, U2.4, U2.9, U3.3
GNDD: ADC1.GND, ICSP1.6, J1.G, J2.6, J2.7, J4.4, NT1.2, Q3.1, Q4.1, Q5.1, Q6.1, Q7.1, R12.1, SHLD1.1, U6.4, U7.4, VR1.1, VR2.1, VR3.1, VR4.1
unnamed: C1.1, J1.T, R3.1
unnamed: C1.2, R2.1
unnamed: C2.1, U1.6, U2.2, U2.3
unnamed: C2.2, JP2.2
unnamed: D1.1, Q4.3, Q5.3
unnamed: D1.2, D2.2, R11.2, R13.2
unnamed: D2.1, Q6.3
unnamed: D3.1, Q7.3
unnamed: D3.2, R14.2
unnamed: J1.S, R1.2
unnamed: JP1.2, R2.2
unnamed: JP3.1, R8.2
unnamed: JP3.2, Q2.2, U5.2, U5.3, U6.5
unnamed: Q1.1, U2.8, U3.5
unnamed: Q1.2, U4.2, U4.3, U7.7
unnamed: Q2.1, U1.1, U1.5, U3.4
unnamed: Q3.2, R5.1, U2.5
unnamed: Q3.3, Q4.2, R10.2
unnamed: Q7.2, R12.2, R13.1
unnamed: R3.2, U2.1
unnamed: R6.1, R7.1, U1.10, U3.2
unnamed: R8.1, U6.6, U7.5
unnamed: U4.1, U6.7
unnamed: U5.1, U7.6
unnamed: U6.8, U7.8

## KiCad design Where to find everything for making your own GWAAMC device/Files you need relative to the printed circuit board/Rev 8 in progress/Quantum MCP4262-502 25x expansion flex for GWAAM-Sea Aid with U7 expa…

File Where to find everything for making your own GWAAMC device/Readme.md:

[Schematic in PDF](https://github.com/kenneth558/plant_resistance_primary_perception/blob/Free/Where%20to%20find%20everything%20for%20making%20your%20own%20GWAAMC%20device/schematic.pdf)

[More CAD renderings showing components already placed](https://github.com/kenneth558/plant_resistance_primary_perception/tree/Free/Where%20to%20find%20everything%20for%20making%20your%20own%20GWAAMC%20device/Construction%20details)

[See the bare boards](https://github.com/kenneth558/plant_resistance_primary_perception/blob/Free/Where%20to%20find%20everything%20for%20making%20your%20own%20GWAAMC%20device/Files%20you%20need%20relative%20to%20the%20printed%20circuit%20board/View%20bare%20board.md)

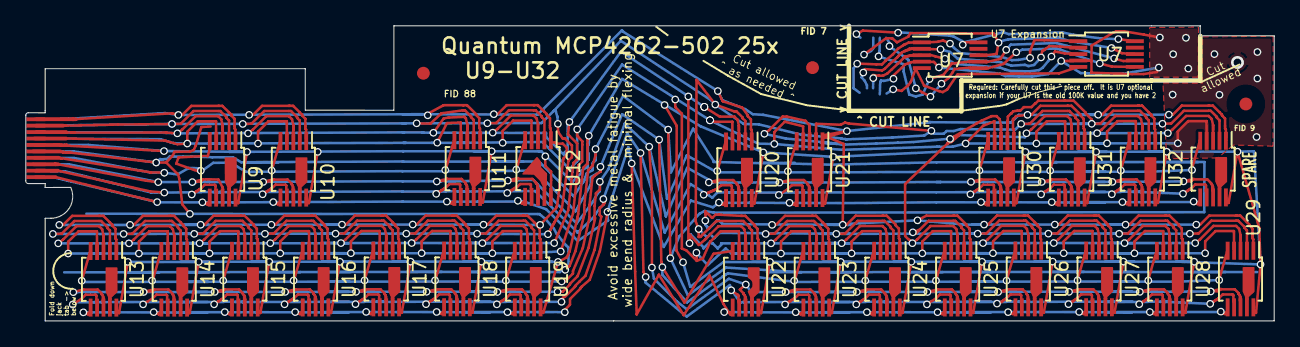
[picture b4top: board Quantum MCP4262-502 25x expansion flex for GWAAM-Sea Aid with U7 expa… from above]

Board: 2 copper layers, 97.0 x 22.9 mm, 32 parts (1 on the bottom side), 9 nets.

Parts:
FID 7, FID 9, FID 88: Fiducial_1mm_Mask3mm
SPARE: MCP4262-502E/UN; MSOP-10_3x3mm_P0.5mm
U7, U7#2, U9, U10, U11, U12, U13, U14, U15, U16, U17, U18, U19, U20, U21, U22, U23, U24, U25, U26, U27, U28, U29, U30, U31, U32: MCP4262-502E/UN; MSOP-10_3x3mm_P0.5mm
U7footprint: MCP4262-502E/UN; MSOP-10_3x3mm_P0.5mm_flipped
mates to TE_1-2328702-0: VAL**; TE_1-2328702-0_card_edge

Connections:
+5V: SPARE.10, U7.10, U7#2.10, U7footprint.10, U9.10, U10.10, U11.10, U12.10, U13.10, U14.10, U15.10, U16.10, U17.10, U18.10, U19.10, U20.10, U21.10, U22.10, U23.10, U24.10, U25.10, U26.10, U27.10, U28.10, U29.10, U30.10, U31.10, U32.10, mates to TE_1-2328702-0.6
/8: SPARE.1, U7.1, U7#2.1, U7footprint.1, U9.1, U10.1, U11.1, U12.1, U13.1, U14.1, U15.1, U16.1, U17.1, U18.1, U19.1, U20.1, U21.1, U22.1, U23.1, U24.1, U25.1, U26.1, U27.1, U28.1, U29.1, U30.1, U31.1, U32.1, mates to TE_1-2328702-0.10
/MOSI(1): SPARE.3, U7.3, U7#2.3, U7footprint.3, U9.3, U10.3, U11.3, U12.3, U13.3, U14.3, U15.3, U16.3, U17.3, U18.3, U19.3, U20.3, U21.3, U22.3, U23.3, U24.3, U25.3, U26.3, U27.3, U28.3, U29.3, U30.3, U31.3, U32.3, mates to TE_1-2328702-0.8
/SCK(1): SPARE.2, U7.2, U7#2.2, U7footprint.2, U9.2, U10.2, U11.2, U12.2, U13.2, U14.2, U15.2, U16.2, U17.2, U18.2, U19.2, U20.2, U21.2, U22.2, U23.2, U24.2, U25.2, U26.2, U27.2, U28.2, U29.2, U30.2, U31.2, U32.2, mates to TE_1-2328702-0.9
/U8-Pad5: SPARE.5, U7.5, U7#2.5, U7footprint.5, U9.5, U10.5, U11.5, U12.5, U13.5, U14.5, U15.5, U16.5, U17.5, U18.5, U19.5, U20.5, U21.5, U22.5, U23.5, U24.5, U25.5, U26.5, U27.5, U28.5, U29.5, U30.5, U31.5, U32.5, mates to TE_1-2328702-0.4
/U8-Pad6: SPARE.6, U7.6, U7#2.6, U7footprint.6, U9.6, U10.6, U11.6, U12.6, U13.6, U14.6, U15.6, U16.6, U17.6, U18.6, U19.6, U20.6, U21.6, U22.6, U23.6, U24.6, U25.6, U26.6, U27.6, U28.6, U29.6, U30.6, U31.6, U32.6, mates to TE_1-2328702-0.1
/U8-Pad7: SPARE.7, U7.7, U7#2.7, U7footprint.7, U9.7, U10.7, U11.7, U12.7, U13.7, U14.7, U15.7, U16.7, U17.7, U18.7, U19.7, U20.7, U21.7, U22.7, U23.7, U24.7, U25.7, U26.7, U27.7, U28.7, U29.7, U30.7, U31.7, U32.7, mates to TE_1-2328702-0.2
/U8-Pad8: SPARE.8, U7.8, U7#2.8, U7footprint.8, U9.8, U10.8, U11.8, U12.8, U13.8, U14.8, U15.8, U16.8, U17.8, U18.8, U19.8, U20.8, U21.8, U22.8, U23.8, U24.8, U25.8, U26.8, U27.8, U28.8, U29.8, U30.8, U31.8, U32.8, mates to TE_1-2328702-0.3
GNDD: SPARE.4, U7.4, U7#2.4, U7footprint.4, U9.4, U10.4, U11.4, U12.4, U13.4, U14.4, U15.4, U16.4, U17.4, U18.4, U19.4, U20.4, U21.4, U22.4, U23.4, U24.4, U25.4, U26.4, U27.4, U28.4, U29.4, U30.4, U31.4, U32.4, mates to TE_1-2328702-0.7

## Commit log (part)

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2020-02-27 Uploading main and aux gerbers & masks
2020-03-10 Create v1.0 combined main plus aux on single board
2020-03-10 Create new
2020-03-10 Most advanced board design
    This board design can simplify ordering for you by eliminating the need to manually panelize the two boards onto a single panel to save fabricating $
2020-03-11 Create temp
2020-03-11 If you find it awkward to order separate boards...
    These files combine main and auxiliary (stacking) boards into one if you find that more convenient to work with. Once the components are soldered down (or before, if you prefer) the boards should eve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
2020-03-11 Main and aux (stacker expansion) in here are separate
    This set of files have the main board separate from each other, but if you want to order and construct everything as only one board, use the files in the sub-directory appropriately named for the sin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
2020-03-11 These files if you find it awkward to order separate boards...
    These files combine main and auxiliary (stacking) boards into one if you find that more convenient to work with. Once the components are soldered down (or before, if you prefer) the boards should eve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
2020-03-24 Create DIY stencil from aluminum can
2020-03-24 Update DIY stencil from aluminum can
2020-03-25 KiCAD format component place
2020-04-11 Main board section only
2020-04-11 One file holding both main and aux boards
2020-05-06 Find FreeCAD Files at https://drive.google.com/drive/folders/1ULUulqfxnpEf3x2tb2fJzP_oNYusfH2K?usp=sharing
    Find FreeCAD Files for pick and place cassette at https://drive.google.com/drive/folders/1ULUulqfxnpEf3x2tb2fJzP_oNYusfH2K?usp=sharing
2020-05-06 Find FreeCAD Files at https://drive.google.com/drive/folders/1ULUulqf… …xnpEf3x2tb2fJzP_oNYusfH2K?usp=sharing
    Find FreeCAD Files for pick and place cassette at https://drive.google.com/drive/folders/1ULUulqfxnpEf3x2tb2fJzP_oNYusfH2K?usp=sharing
2020-05-09 Find FreeCAD Files at https://drive.google.com/drive/folders/1ULUulqf… … ……xnpEf3x2tb2fJzP_oNYusfH2K?usp=sharing
    Find FreeCAD Files for pick and place cassette at https://drive.google.com/drive/folders/1ULUulqfxnpEf3x2tb2fJzP_oNYusfH2K?usp=sharing
2020-05-09 Find FreeCAD Files at https://drive.google.com/drive/folders/1ULUulqf…… … … ……xnpEf3x2tb2fJzP_oNYusfH2K?usp=sharing
    Find FreeCAD Files at https://drive.google.com/drive/folders/1ULUulqf……
    … … ……xnpEf3x2tb2fJzP_oNYusfH2K?usp=sharing
2020-05-09 Find FreeCAD Files for pick and place cassette at https://drive.google.com/drive/folders/1ULUulqfxnpEf3x2tb2fJzP_oNYusfH2K?usp=sharing
    Find FreeCAD Files for pick and place cassette at https://drive.google.com/drive/folders/1ULUulqfxnpEf3x2tb2fJzP_oNYusfH2K?usp=sharing
2020-05-10 Create Risks; Required Skills and Knowledge
2020-05-10 Open this in a spreadsheet
2020-12-27 Clean up minor development alerts

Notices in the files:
Where to find everything for making your own GWAAMC device/Construction details/uno shield v1.0 project SMD with aux board.kicad_pcb:
GWAAMC Training Aid (C) 2020
